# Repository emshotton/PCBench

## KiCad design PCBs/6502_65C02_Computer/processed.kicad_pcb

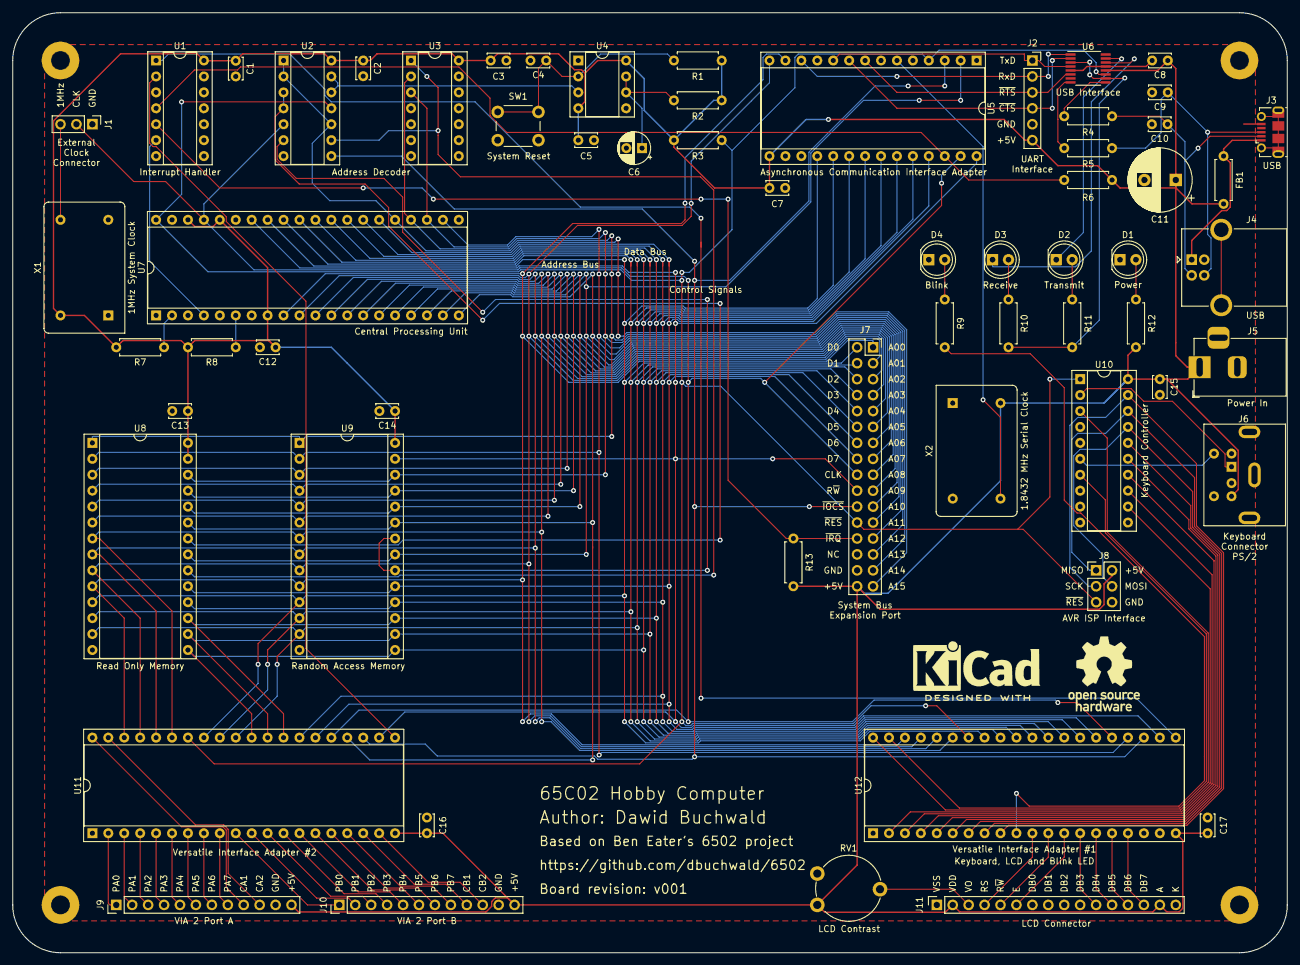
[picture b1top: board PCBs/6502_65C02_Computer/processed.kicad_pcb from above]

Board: 2 copper layers, 203.2 x 149.9 mm, 62 parts (0 on the bottom side), 102 nets.

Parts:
C1, C2, C3, C4, C5, C7, C12, C13, C14, C15, C16, C17: 0.1uF; C_Disc_D3.4mm_W2.1mm_P2.50mm
C6: 10uF; CP_Radial_D5.0mm_P2.50mm
C8: 10nF; C_Disc_D3.4mm_W2.1mm_P2.50mm
C9, C10: 47pF; C_Disc_D3.4mm_W2.1mm_P2.50mm
C11: 1000uF; CP_Radial_D10.0mm_P5.00mm
D1: PWR; LED_D5.0mm_Clear
D2: TX; LED_D5.0mm_Clear
D3: RX; LED_D5.0mm_Clear
D4: BLINK; LED_D5.0mm_Clear
FB1: Ferrite_Bead_Small; R_Axial_DIN0207_L6.3mm_D2.5mm_P7.62mm_Horizontal
J1: CLK Jumper; PinHeader_1x03_P2.54mm_Vertical
J2: Optional UART Port; PinSocket_1x06_P2.54mm_Vertical
J3: USB_B_Micro; USB_Micro-B_Molex-105017-0001
J4: USB_B; USB_B_OST_USB-B1HSxx_Horizontal
J5: Power Connector; BarrelJack_Horizontal
J6: Mini-DIN-6; mini_din-6
J7: Expansion port; PinSocket_2x16_P2.54mm_Vertical
J8: AVR-ISP-10; PinHeader_2x03_P2.54mm_Vertical
J9: VIA2PA; PinHeader_1x12_P2.54mm_Vertical
J10: VIA2PB; PinHeader_1x12_P2.54mm_Vertical
J11: LCD Connector; PinSocket_1x16_P2.54mm_Vertical
R1: 1M; R_Axial_DIN0207_L6.3mm_D2.5mm_P7.62mm_Horizontal
R2: 47K; R_Axial_DIN0207_L6.3mm_D2.5mm_P7.62mm_Horizontal
R3: 10K; R_Axial_DIN0207_L6.3mm_D2.5mm_P7.62mm_Horizontal
R4, R5: 27; R_Axial_DIN0207_L6.3mm_D2.5mm_P7.62mm_Horizontal
R6, R7, R8, R13: 4K7; R_Axial_DIN0207_L6.3mm_D2.5mm_P7.62mm_Horizontal
R9, R10, R11, R12: 270; R_Axial_DIN0207_L6.3mm_D2.5mm_P7.62mm_Horizontal
RV1: 10K; Potentiometer_Piher_PT-10-V10_Vertical
SW1: RESET; SW_PUSH_6mm_H4.3mm
U1: 74HC21; DIP-14_W7.62mm_Socket
U2: 74HC00; DIP-14_W7.62mm_Socket
U3: 74HC02; DIP-14_W7.62mm_Socket
U4: NE555; DIP-8_W7.62mm_Socket
U5: 65C51N; DIP-28_W15.24mm_Socket
U6: FT230XS; SSOP-16_3.9x4.9mm_P0.635mm_long_pads
U7: 65C02S; DIP-40_W15.24mm_Socket
U8: 28C256; DIP-28_W15.24mm_Socket
U9: 62256; DIP-28_W15.24mm_Socket
U10: ATtiny4313-PU; DIP-20_W7.62mm_Socket
U11, U12: 65C22S; DIP-40_W15.24mm_Socket
X1: 1MHz; Oscillator_DIP-14
X2: 1.8432MHz; Oscillator_DIP-14

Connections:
+5V: C1.1, C2.1, C3.1, C5.1, C7.1, C8.1, C11.1, C12.1, C13.1, C14.1, C15.1, C16.1, C17.1, FB1.1, J2.6, J5.1, J6.4, J7.32, J8.2, J9.12, J10.12, J11.2, J11.15, R1.1, R2.1, R3.1, R6.1, R7.2, R8.2, R12.1, R13.1, RV1.1, U1.14, U2.14, U3.14, U4.4, U4.8, U5.15, U6.12, U7.8, U7.36, U7.38, U8.27, U8.28, U9.28, U10.20, U11.20, U12.20, X1.14, X2.14
/6502 Peripherals/v1pa0: U10.12, U12.2
/6502 Peripherals/v1pa1: U10.13, U12.3
/6502 Peripherals/v1pa2: U10.14, U12.4
/6502 Peripherals/v1pa3: U10.15, U12.5
/6502 Peripherals/v1pa4: U10.16, U12.6
/6502 Peripherals/v1pa5: J8.4, U10.17, U12.7
/6502 Peripherals/v1pa6: J8.1, U10.18, U12.8
/6502 Peripherals/v1pa7: J8.3, U10.19, U12.9
/6502 Peripherals/v1pa8: U10.3, U12.40
/6502 Peripherals/v1pa9: U10.7, U12.39
/6502 Peripherals/v1pb0: R9.1, U12.10
/6502 Peripherals/v1pb1: J11.4, U12.11
/6502 Peripherals/v1pb2: J11.5, U12.12
/6502 Peripherals/v1pb3: J11.6, U12.13
/6502 Peripherals/v1pb4: J11.11, U12.14
/6502 Peripherals/v1pb5: J11.12, U12.15
/6502 Peripherals/v1pb6: J11.13, U12.16
/6502 Peripherals/v1pb7: J11.14, U12.17
/6502 Peripherals/v2pa0: J9.1, U11.2
/6502 Peripherals/v2pa1: J9.2, U11.3
/6502 Peripherals/v2pa2: J9.3, U11.4
/6502 Peripherals/v2pa3: J9.4, U11.5
/6502 Peripherals/v2pa4: J9.5, U11.6
/6502 Peripherals/v2pa5: J9.6, U11.7
/6502 Peripherals/v2pa6: J9.7, U11.8
/6502 Peripherals/v2pa7: J9.8, U11.9
/6502 Peripherals/v2pa8: J9.9, U11.40
/6502 Peripherals/v2pa9: J9.10, U11.39
/6502 Peripherals/v2pb0: J10.1, U11.10
/6502 Peripherals/v2pb1: J10.2, U11.11
/6502 Peripherals/v2pb2: J10.3, U11.12
/6502 Peripherals/v2pb3: J10.4, U11.13
/6502 Peripherals/v2pb4: J10.5, U11.14
/6502 Peripherals/v2pb5: J10.6, U11.15
/6502 Peripherals/v2pb6: J10.7, U11.16
/6502 Peripherals/v2pb7: J10.8, U11.17
/6502 Peripherals/v2pb8: J10.9, U11.18
/6502 Peripherals/v2pb9: J10.10, U11.19
CLK: J1.2, J7.18, U2.5, U5.27, U7.37, U11.25, U12.25
CLKOUT: J1.3, X1.8
GND: C1.2, C2.2, C3.2, C4.2, C5.2, C6.2, C7.2, C8.2, C9.2, C10.2, C11.2, C12.2, C13.2, C14.2, C15.2, C16.2, C17.2, D1.1, D4.1, J1.1, J2.5, J3.5, J4.4, J5.2, J6.3, J7.30, J8.6, J9.11, J10.11, J11.1, J11.7, J11.8, J11.9, J11.10, J11.16, RV1.3, SW1.1, U1.7, U1.9, U1.10, U1.12, U1.13, U2.7, U3.5, U3.6, U3.7, U3.8, U3.9, U3.11, U3.12, U4.1, U5.1, U5.16, U5.17, U6.5, U6.13, U7.21, U8.14, U9.14, U10.10, U11.1, U12.1, X1.7, X2.7
KBCLK: J6.5, U10.6
KBDAT: J6.1, U10.2
unnamed: C4.1, R1.2, SW1.2, U4.2
unnamed: C6.1, R2.2, U4.6, U4.7
unnamed: D1.2, R12.2
unnamed: D2.1, U6.15
unnamed: D2.2, R11.2
unnamed: D3.1, U6.14
unnamed: D3.2, R10.2
unnamed: D4.2, R9.2
unnamed: FB1.2, J3.1, J4.1
unnamed: J11.3, RV1.2
unnamed: R7.1, U7.2
unnamed: R8.1, U7.6
unnamed: R10.1, R11.1, U6.3, U6.10
unnamed: U2.12, U2.13, U4.3
PUSBD+: C9.1, J3.3, J4.3, R5.2
PUSBD-: C10.1, J3.2, J4.2, R4.2
RS232CLK: U5.6, X2.8
RxD: J2.2, U5.12, U6.1
R~W: J7.20, U5.28, U7.34, U9.27, U11.22, U12.22
TxD: J2.1, U5.10, U6.4
USBD+: R5.1, U6.8
USBD-: R4.1, U6.9
a0: J7.1, U5.13, U7.9, U8.10, U9.10, U11.38, U12.38
a1: J7.3, U5.14, U7.10, U8.9, U9.9, U11.37, U12.37
a2: J7.5, U7.11, U8.8, U9.8, U11.36, U12.36
a3: J7.7, U7.12, U8.7, U9.7, U11.35, U12.35
a4: J7.9, U7.13, U8.6, U9.6
a5: J7.11, U7.14, U8.5, U9.5
a6: J7.13, U7.15, U8.4, U9.4
a7: J7.15, U7.16, U8.3, U9.3
a8: J7.17, U7.17, U8.25, U9.25
a9: J7.19, U7.18, U8.24, U9.24
a10: J7.21, U5.2, U7.19, U8.21, U9.21
a11: J7.23, U7.20, U8.23, U9.23, U11.24
a12: J7.25, U7.22, U8.2, U9.2, U12.24
a13: J7.27, U3.3, U7.23, U8.26, U9.26
a14: J7.29, U3.2, U7.24, U8.1, U9.1
a15: J7.31, U2.1, U2.2, U2.10, U7.25
d0: J7.2, U5.18, U7.33, U8.11, U9.11, U11.33, U12.33
d1: J7.4, U5.19, U7.32, U8.12, U9.12, U11.32, U12.32
d2: J7.6, U5.20, U7.31, U8.13, U9.13, U11.31, U12.31
d3: J7.8, U5.21, U7.30, U8.15, U9.15, U11.30, U12.30
d4: J7.10, U5.22, U7.29, U8.16, U9.16, U11.29, U12.29
d5: J7.12, U5.23, U7.28, U8.17, U9.17, U11.28, U12.28
d6: J7.14, U5.24, U7.27, U8.18, U9.18, U11.27, U12.27
d7: J7.16, U5.25, U7.26, U8.19, U9.19, U11.26, U12.26
~AIRQ: R6.2, U1.4, U5.26
~CTS: J2.4, U5.9, U6.2
~IOCS: J7.22, U2.8, U5.3, U11.23, U12.23
~IRQ: U1.6, U7.4
~IRQX: J7.26, R13.2, U1.5
~RAM_CS: U2.6, U9.20, U9.22
~RES: J7.24, J8.5, R3.2, U2.11, U5.4, U6.11, U7.40, U10.1, U11.34, U12.34
~ROM_CS: U2.9, U3.1, U8.20
~ROM_OE: U2.3, U2.4, U8.22
~RTS: J2.3, U5.8, U6.6
~V1IRQ: U1.1, U12.21
~V2IRQ: U1.2, U11.21

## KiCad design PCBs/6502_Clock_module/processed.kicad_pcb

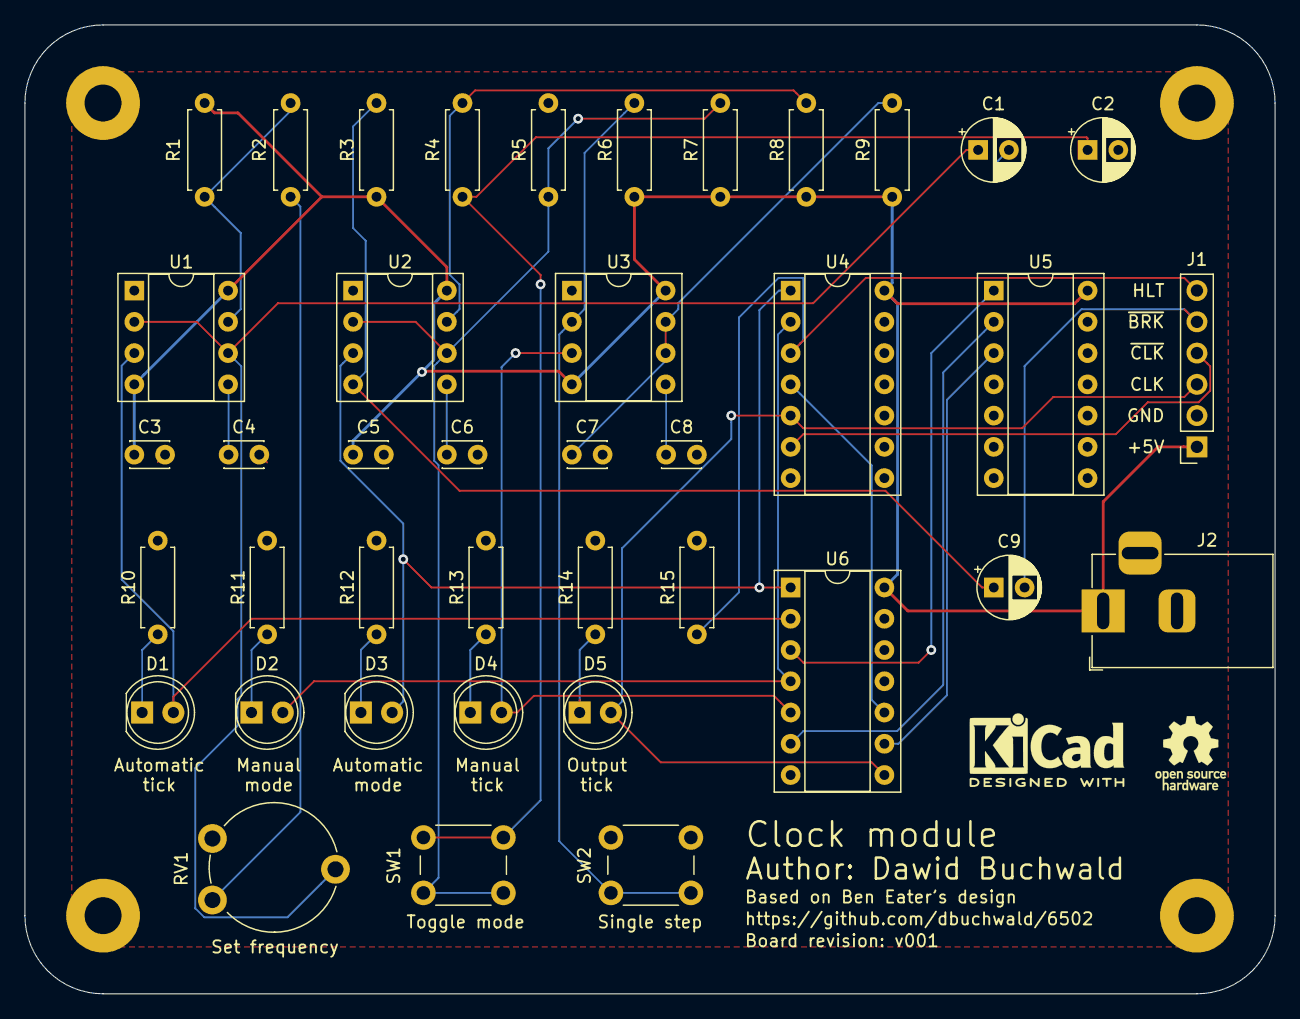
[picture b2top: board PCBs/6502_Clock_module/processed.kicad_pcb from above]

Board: 2 copper layers, 101.6 x 78.7 mm, 40 parts (0 on the bottom side), 31 nets.

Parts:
C1, C2, C9: 1uF; CP_Radial_D5.0mm_P2.50mm
C3: 0.01uF; C_Disc_D3.0mm_W2.0mm_P2.50mm
C4, C5, C6, C7, C8: 0.1uF; C_Disc_D3.0mm_W2.0mm_P2.50mm
D1: YELLOW_A; LED_D5.0mm
D2: RED; LED_D5.0mm
D3: GREEN; LED_D5.0mm
D4: YELLOW_M; LED_D5.0mm
D5: BLUE; LED_D5.0mm
J1: Conn_01x06_Female; PinSocket_1x06_P2.54mm_Vertical
J2: Power Input; BarrelJack_Horizontal
R1, R2, R3, R6, R8, R15: 1K; R_Axial_DIN0207_L6.3mm_D2.5mm_P7.62mm_Horizontal
R4: 100K; R_Axial_DIN0207_L6.3mm_D2.5mm_P7.62mm_Horizontal
R5, R7: 10K; R_Axial_DIN0207_L6.3mm_D2.5mm_P7.62mm_Horizontal
R9: 1M; R_Axial_DIN0207_L6.3mm_D2.5mm_P7.62mm_Horizontal
R10, R11, R12, R13, R14: 220; R_Axial_DIN0207_L6.3mm_D2.5mm_P7.62mm_Horizontal
RV1: 1M; Potentiometer_Piher_PT-10-V10_Vertical
SW1: Mode; SW_PUSH_6mm
SW2: Step; SW_PUSH_6mm
U1, U2, U3: NE555; DIP-8_W7.62mm_Socket
U4: 74LS04; DIP-14_W7.62mm_Socket
U5: 74LS32; DIP-14_W7.62mm_Socket
U6: 74LS08; DIP-14_W7.62mm_Socket

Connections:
AUTO: D1.2, U1.3, U6.2
CLK: D5.2, J1.3, U4.5, U6.8
GND: C1.2, C2.2, C3.2, C4.2, C5.2, C6.2, C7.2, C8.2, J1.2, J2.2, R5.2, R10.2, R11.2, R12.2, R13.2, R14.2, R15.2, SW2.1, U1.1, U2.1, U3.1, U4.7, U5.7, U6.7
HLT: J1.6, R15.1, U4.3
MAN: D4.2, U3.3, U6.5
MODE: D3.2, U2.3, U4.1, U6.1
unnamed: C1.1, RV1.2, U1.2, U1.6
unnamed: C2.1, R4.2, SW1.1
unnamed: C4.1, U1.5
unnamed: C6.1, U2.5
unnamed: C7.1, R9.2, U3.6, U3.7
unnamed: C8.1, U3.5
unnamed: C9.1, R3.2, U2.4
unnamed: D1.1, R10.1
unnamed: D2.1, R11.1
unnamed: D3.1, R12.1
unnamed: D4.1, R13.1
unnamed: D5.1, R14.1
unnamed: R1.2, R2.1, U1.7
unnamed: R2.2, RV1.1
unnamed: R4.1, R8.2, U2.7
unnamed: R5.1, R7.2, SW1.2, U2.2, U2.6
unnamed: R6.2, SW2.2, U3.2
unnamed: U4.4, U6.10
unnamed: U5.1, U6.3
unnamed: U5.2, U6.6
unnamed: U5.3, U6.9
VCC: C3.1, C5.1, J1.1, J2.1, R1.1, R3.1, R6.1, R7.1, R8.1, R9.1, U1.4, U1.8, U2.8, U3.4, U3.8, U4.14, U5.14, U6.14
~BRK: C9.2, J1.5
~CLK: J1.4, U4.6
~MODE: D2.2, U4.2, U6.4

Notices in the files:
PCBs/8bit-cpu_programming_interface/processed.kicad_pcb:
2020 copyright Federico Scozzafava https://github.com/vascofazza/8bit_cpu
